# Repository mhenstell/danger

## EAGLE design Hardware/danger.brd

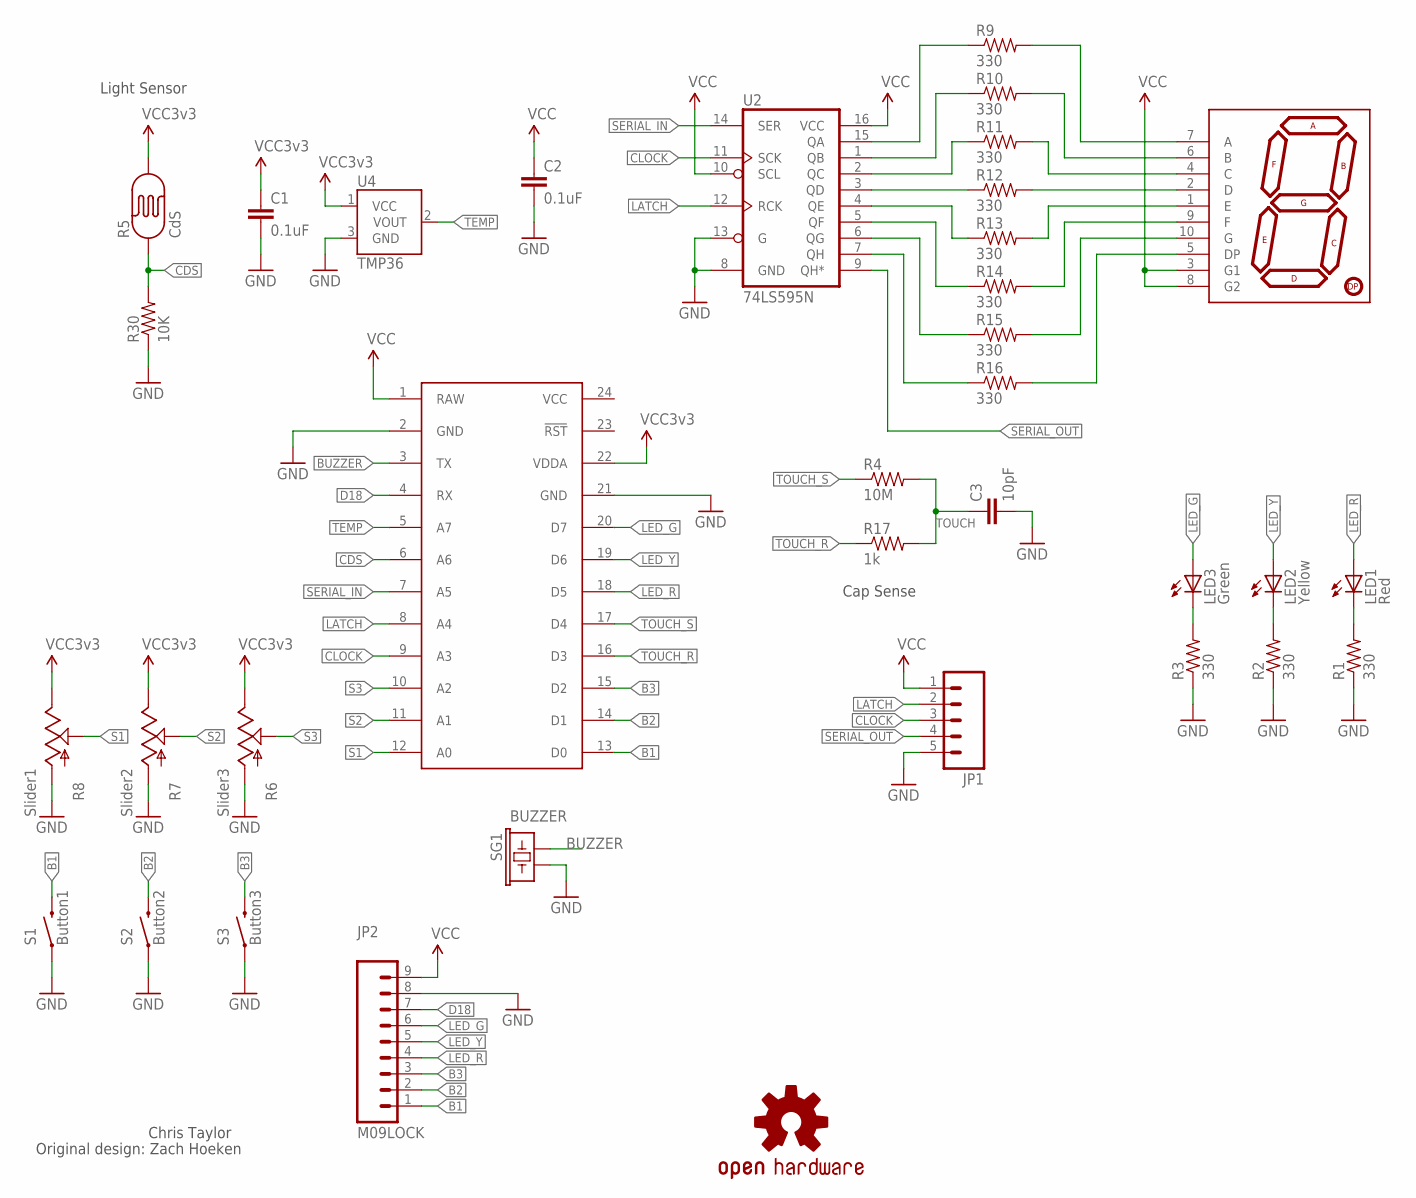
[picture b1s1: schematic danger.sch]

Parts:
C1, C2: 0.1uF; CAP-PTH-SMALL2
C3: 10pF; CAP-PTH-SMALL2
IC1: SPARK_CORECORE; SPARK_CORE
JP1: M05PTH; 1X05
JP2: M09LOCK; 1X09_LOCK
LED1: Red; LED5MM
LED2: Yellow; LED5MM
LED3: Green; LED5MM
R1, R2, R3, R9, R10, R11, R12, R13, R14, R15, R16: 330; AXIAL-0.3
R4: 10M; AXIAL-0.3
R5: CdS; PHOTOCELL
R6: Slider3; SLIDER
R7: Slider2; SLIDER
R8: Slider1; SLIDER
R17: 1k; AXIAL-0.3
R30: 10K; AXIAL-0.3
S1: Button1; TACTILE-PTH-12MM
S2: Button2; TACTILE-PTH-12MM
S3: Button3; TACTILE-PTH-12MM
SG1: BUZZER; BUZZER-12MM
U2: 74LS595N; DIL16
U4: TMP36; TO-92
U6: 7-SEGMENT-DISPLAY-1"-RED; 7-SEGMENT-1"PTH
U$2: OSHW-LOGOM; OSHW-LOGO-M

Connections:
B1: IC1.13 (D0), JP2.1, S1.3 (2)
B2: IC1.14 (D1), JP2.2, S2.3 (2)
B3: IC1.15 (D2), JP2.3, S3.3 (2)
BUZZER: IC1.3 (TX), SG1.+ (1)
CDS: IC1.6 (A6), R5.1, R30.P$2 (2)
CLOCK: IC1.9 (A3), JP1.3, U2.11 (SCK)
D18: IC1.4 (RX), JP2.7
GND: C1.2, C2.2, C3.2, IC1.2 (GND), IC1.21 (GND), JP1.5, JP2.8, R1.P$1 (1), R2.P$1 (1), R3.P$1 (1), R6.3 (A), R7.3 (A), R8.3 (A), R30.P$1 (1), S1.1, S2.1, S3.1, SG1.- (2), U2.8 (GND), U2.13 (G), U4.3 (GND)
LATCH: IC1.8 (A4), JP1.2, U2.12 (RCK)
LED_G: IC1.20 (D7), JP2.6, LED3.A
LED_R: IC1.18 (D5), JP2.4, LED1.A
LED_Y: IC1.19 (D6), JP2.5, LED2.A
unnamed: R9.P$1 (1), U2.15 (QA)
unnamed: LED1.K (C), R1.P$2 (2)
unnamed: R10.P$1 (1), U2.1 (QB)
unnamed: R11.P$1 (1), U2.2 (QC)
unnamed: R12.P$1 (1), U2.3 (QD)
unnamed: R13.P$1 (1), U2.4 (QE)
unnamed: R14.P$1 (1), U2.5 (QF)
unnamed: R15.P$1 (1), U2.6 (QG)
unnamed: R16.P$1 (1), U2.7 (QH)
unnamed: R9.P$2 (2), U6.7 (A)
unnamed: R10.P$2 (2), U6.6 (B)
unnamed: R11.P$2 (2), U6.4 (C)
unnamed: R12.P$2 (2), U6.2 (D)
unnamed: R13.P$2 (2), U6.1 (E)
unnamed: R14.P$2 (2), U6.9 (F)
unnamed: R15.P$2 (2), U6.10 (G)
unnamed: R16.P$2 (2), U6.5 (DP)
unnamed: LED2.K (C), R2.P$2 (2)
unnamed: LED3.K (C), R3.P$2 (2)
S1: IC1.12 (A0), R8.2A (S)
S2: IC1.11 (A1), R7.2A (S)
S3: IC1.10 (A2), R6.2A (S)
SERIAL_IN: IC1.7 (A5), U2.14 (SER)
SERIAL_OUT: JP1.4, U2.9 (QH*)
TEMP: IC1.5 (A7), U4.2 (VOUT)
TOUCH: C3.1, R4.P$2 (2), R17.P$2 (2)
TOUCH_R: IC1.16 (D3), R17.P$1 (1)
TOUCH_S: IC1.17 (D4), R4.P$1 (1)
VCC: C2.1, IC1.1 (RAW), IC1.24 (VCC), JP1.1, JP2.9, U2.10 (SCL), U2.16 (VCC), U6.3 (G1), U6.8 (G2)
VCC3V3: C1.1, IC1.22 (VDDA), R5.2, R6.1 (E), R7.1 (E), R8.1 (E), U4.1 (VCC)

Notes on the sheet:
Light Sensor
Cap Sense
Chris Taylor
Original design: Zach Hoeken

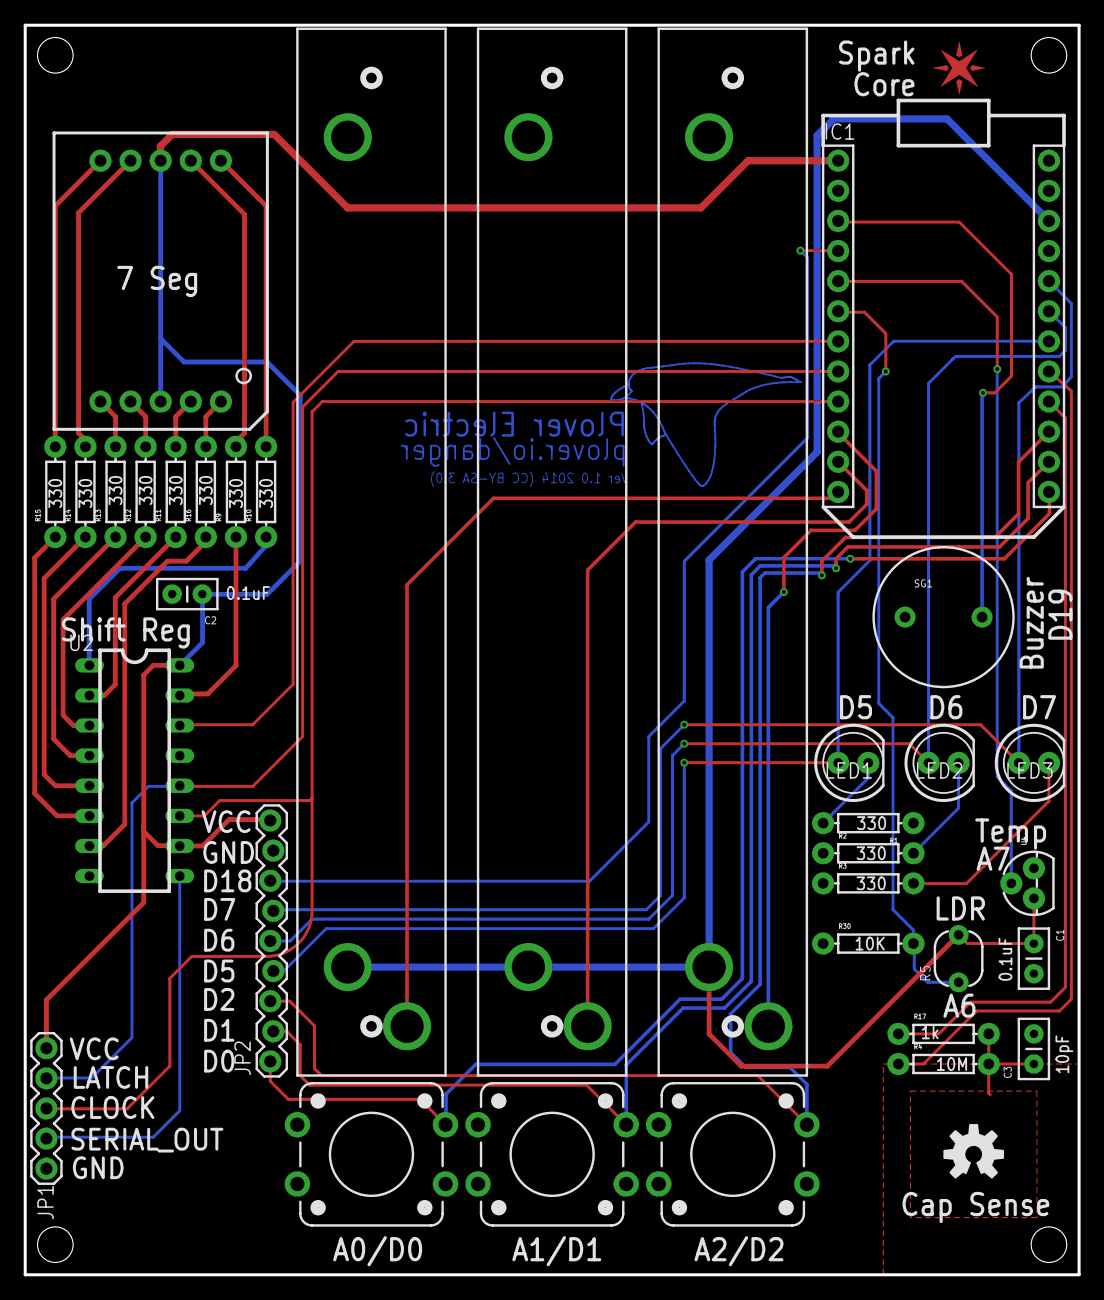
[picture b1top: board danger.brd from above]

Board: 2 copper layers, 88.9 x 105.4 mm, 36 parts (0 on the bottom side), 42 nets.

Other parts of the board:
U$1: SPARK_LOGO_PLUS_PLANE

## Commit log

2014-08-09 init
2014-08-12 redid based on sparkfun design
2014-08-12 finished routing
2014-08-13 added headers
2014-08-19 added logo, v1
2014-08-19 moving files
2014-08-19 fixed logo bStop, still needs silks fixed
2014-08-19 made text bigger

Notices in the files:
Hardware/danger.brd:
Ver 1.0 2014 (CC BY-SA 3.0)
parts and their libraries:
SparkFun-Sensors: Licensing: CC v3.0 Share-Alike You are welcome to use this library for commercial purposes.
SparkFun-Connectors: Licensing: Creative Commons ShareAlike 4.0 International - https://creativecommons.org/licenses/by-sa/4.0
